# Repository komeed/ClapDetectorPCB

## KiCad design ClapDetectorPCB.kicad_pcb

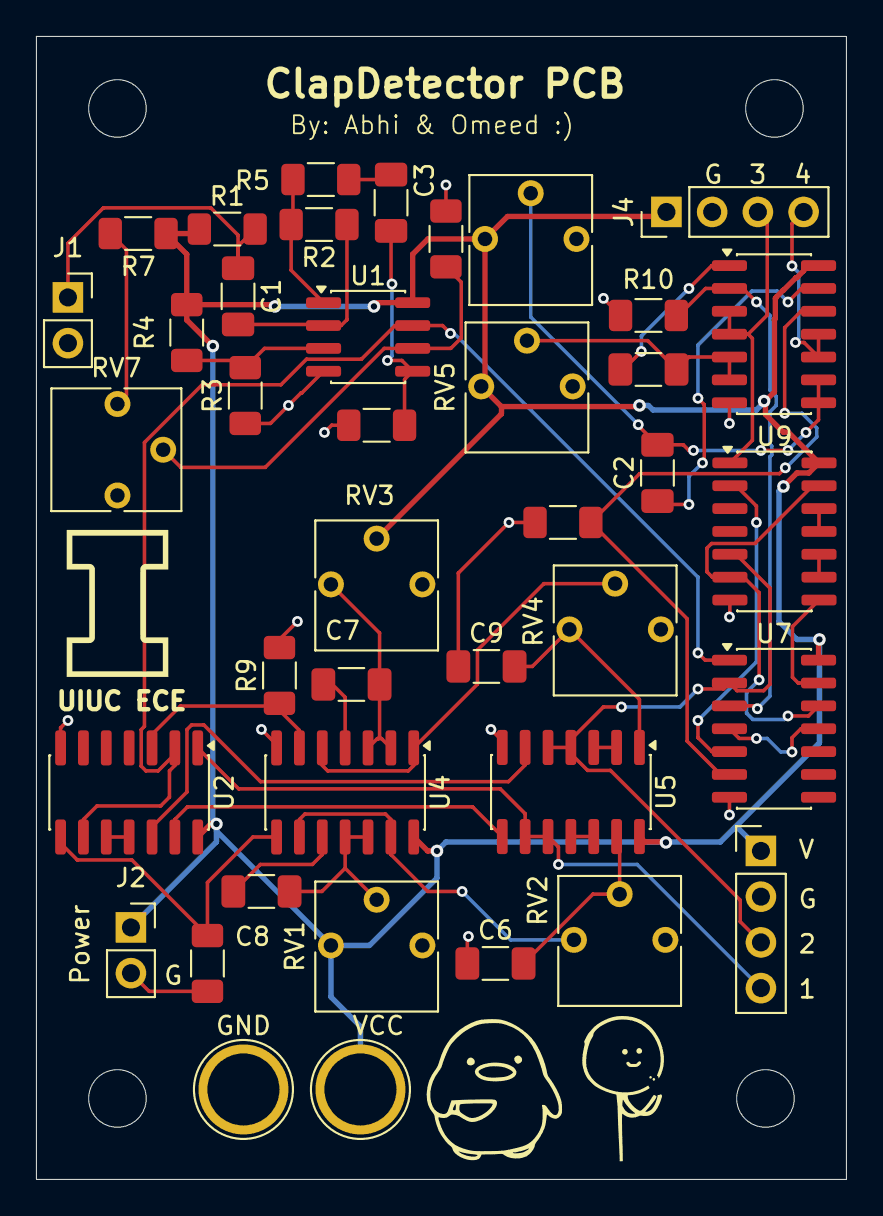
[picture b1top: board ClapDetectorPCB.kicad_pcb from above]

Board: 2 copper layers, 45.0 x 63.5 mm, 40 parts (0 on the bottom side), 42 nets.

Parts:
C1: 10nF; C_1206_3216Metric_Pad1.33x1.80mm_HandSolder
C2, C5, C7, C8: 4.7uF; C_1206_3216Metric_Pad1.33x1.80mm_HandSolder
C3: 2.2uF; C_1206_3216Metric_Pad1.33x1.80mm_HandSolder
C6, C9: 10uF; C_1206_3216Metric_Pad1.33x1.80mm_HandSolder
GND: TestPoint_Plated_Hole_D4.0mm
J1: mic; PinSocket_1x02_P2.54mm_Vertical
J2: Power; PinSocket_1x02_P2.54mm_Vertical
J3: DEBUG_LED; PinHeader_1x04_P2.54mm_Vertical
J4: LED_OUT; PinHeader_1x04_P2.54mm_Vertical
R1, R2: 10kΩ; R_1206_3216Metric_Pad1.30x1.75mm_HandSolder
R3, R4, R6, R8, R9, R10, R16: 100kΩ; R_1206_3216Metric_Pad1.30x1.75mm_HandSolder
R5: 47Ω; R_1206_3216Metric_Pad1.30x1.75mm_HandSolder
R7: 1kΩ; R_1206_3216Metric_Pad1.30x1.75mm_HandSolder
R11: 100Ω; R_1206_3216Metric_Pad1.30x1.75mm_HandSolder
RV1, RV3, RV5, RV6: 300kΩ; Potentiometer_Vishay_T73YP_Vertical
RV2, RV4: 100kΩ; Potentiometer_Vishay_T73YP_Vertical
RV7: 10kΩ; Potentiometer_Vishay_T73YP_Vertical
U1: OP-AMP; SOIC-8_3.9x4.9mm_P1.27mm
U2, U7: 74HC08; SOIC-14_3.9x8.7mm_P1.27mm
U4, U8: 74HC02; SOIC-14_3.9x8.7mm_P1.27mm
U5, U9: 74HC14; SOIC-14_3.9x8.7mm_P1.27mm
VCC: TestPoint_Plated_Hole_D4.0mm

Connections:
AND_8: R8.2, U2.8 (CUSTOM_74HC08-8), U4.8 (CUSTOM_74HC02-8)
AND_OUT: C8.1, U4.10 (CUSTOM_74HC02-10)
COUT: C8.2, RV1.2 (CUSTOM_Potentiometer-2), U4.11 (CUSTOM_74HC02-11), U4.12 (CUSTOM_74HC02-12)
CUSTOM_74HC02-4_45: C7.1, U4.4 (CUSTOM_74HC02-4)
CUSTOM_74HC02-5_46: RV4.2 (CUSTOM_Potentiometer-2), U4.1 (CUSTOM_74HC02-1), U4.5 (CUSTOM_74HC02-5)
CUSTOM_74HC02-9_48: RV2.3 (CUSTOM_Potentiometer-3), U4.9 (CUSTOM_74HC02-9), U4.13 (CUSTOM_74HC02-13)
CUSTOM_74HC08-3_5: R9.1, U2.3 (CUSTOM_74HC08-3), U4.6 (CUSTOM_74HC02-6)
CUSTOM_74HC08-10_9: U2.10 (CUSTOM_74HC08-10), U2.11 (CUSTOM_74HC08-11)
CUSTOM_74HC08-12_11: U2.12 (CUSTOM_74HC08-12), U5.6 (CUSTOM_74HC14-6)
CUSTOM_74HC08-13_12: U2.13 (CUSTOM_74HC08-13), U5.8 (CUSTOM_74HC14-8)
CUSTOM_74HC14-2_26: U5.2 (CUSTOM_74HC14-2), U5.3 (CUSTOM_74HC14-3)
CUSTOM_74HC14-10_33: U5.11 (CUSTOM_74HC14-11), U5.12 (CUSTOM_74HC14-12)
CUSTOM_C8-2_55: C7.2, RV3.3 (CUSTOM_Potentiometer-3), U4.2 (CUSTOM_74HC02-2), U4.3 (CUSTOM_74HC02-3)
CUSTOM_Potentiometer-3_20: C9.2, RV4.3 (CUSTOM_Potentiometer-3), U5.1 (CUSTOM_74HC14-1)
DEL: U7.4, U7.11
GND: C6.1, C9.1, GND.1, J1.2, J2.2, J3.2, J4.2, R3.1, R6.1, R8.1, R9.2, R10.2, R11.2, R16.2, U1.4, U2.7 (CUSTOM_74HC08-7), U4.7 (CUSTOM_74HC02-7), U5.7 (CUSTOM_74HC14-7), U7.7, U8.7, U9.7
M2O: J3.3, U5.4 (CUSTOM_74HC14-4), U5.5 (CUSTOM_74HC14-5), U7.2, U9.5
M2OD0: U7.12, U9.6, U9.13
M2OD1: U9.11, U9.12
M2OD2: U9.9, U9.10
M2OD3: U7.13, U9.8
M3AND: R10.1, U7.3, U8.2
M3NOR1O: C5.1, U8.1
M3NOR2I: C5.2, RV5.2, U8.5, U8.6
M3O: J4.3, U8.3, U8.4, U9.1
M3OINV: U7.5, U9.2
M4AND: R16.1, U7.6, U8.12
M4NOR1O: C2.1, U8.13
M4NOR2I: C2.2, RV6.2, U8.8, U8.9
M4NOR2O: J4.4, U8.10, U8.11
MICO: C1.2, R2.1, U1.2
OPAMP1: R2.2, R5.1, U1.1
OPAMP3: R3.2, R4.2, U1.3
OPAMP5: C3.2, R6.2, U1.5
OPAMP6: R11.1, RV7.2 (CUSTOM_Potentiometer-2), U1.6
PATH1: C3.1, R5.2
Poto1: R7.2, RV7.3 (CUSTOM_Potentiometer-3)
VCC: J2.1, J3.1, J4.1, R1.1, R4.1, R7.1, RV1.3 (CUSTOM_Potentiometer-3), RV3.2 (CUSTOM_Potentiometer-2), RV5.3, RV6.3, U1.8, U2.14 (CUSTOM_74HC08-14), U4.14 (CUSTOM_74HC02-14), U5.14 (CUSTOM_74HC14-14), U7.14, U8.14, U9.14, VCC.1
mic: C1.1, J1.1, R1.2
oops: J3.4, U2.1 (CUSTOM_74HC08-1), U5.9 (CUSTOM_74HC14-9), U5.10 (CUSTOM_74HC14-10)
output_c: C6.2, RV2.2 (CUSTOM_Potentiometer-2), U5.13 (CUSTOM_74HC14-13)
vmic: U1.7, U2.2 (CUSTOM_74HC08-2), U2.9 (CUSTOM_74HC08-9), U7.1
